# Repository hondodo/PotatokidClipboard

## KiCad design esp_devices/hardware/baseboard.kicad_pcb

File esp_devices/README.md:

# ESP 设备

本目录存放 Potatokid 自研 ESP32 小屏的设备固件与操作文档。后续新增的 ESP 设备统一放在 `firmware/<设备名>/` 下。

```
esp_devices/
├── README.md                       # 本文档
├── .gitignore                      # 排除 secrets.h / 构建产物
└── firmware/
    └── potatokid_esp/              # ESP32-S3 + 1.3" OLED 小屏
        ├── potatokid_esp.ino       # 固件（Arduino）
        ├── secrets.h.example       # 私密配置模板
        └── secrets.h               # 本地私密配置（不入库）
```

## 1. 硬件

| 项目 | 型号 / 参数 |
|---|---|
| 主控 | ESP32-S3（QFN56 rev0.2，16MB Flash，8MB PSRAM） |
| 串口 | CH343 USB-UART，Linux 下为 `/dev/ttyACM0` |
| 屏幕 | 1.3 寸 OLED，**SH1106** 128x64，I2C，地址 `0x3C` |
| 按键 | 可选 1~8 个轻触按键或干接点；当前面板占用 GPIO4/5/6/7/10/11/12/13 |
| 人体感应 | 可选，输出高电平的人体感应模块（VCC 2.7–12V），OUT 接空闲 RTC GPIO（本版 GPIO7 已被按键占用） |
| 音频 | INMP441 麦克风（I2S 14/15/16）+ MAX98357 功放（I2S 17/18/47），两路独立 |
| 遥控 | 433 接收模块（ASL430D 等，串口模式）D0/TX 接 GPIO21 |

## 2. 接线

### 2.1 屏幕

四根杜邦线，**接线前先断开 USB**：

| OLED 模块 | 接到开发板 |
|---|---|
| VCC | **3V3**（不要接 5V） |
| GND | GND |
| SCL | GPIO9 |
| SDA | GPIO8 |

注意事项：

- 按模块丝印接，不同厂家 4 针顺序不一定是 VCC/GND/SCL/SDA；
- ESP32-S3 没有 GPIO22~25，别照抄 ESP32 老教程；GPIO33~37 被 PSRAM 占用，GPIO19/20 是 USB，都要避开；
- 换引脚只改固件顶部的 `PIN_SDA` / `PIN_SCL` 两个常量；
- 模块自带 4.7k 上拉，杜邦线尽量短。

### 2.2 按键（测试期用杜邦线即可）

当前面板的 8 个槽位与引脚：

| 槽位 | 1 | 2 | 3 | 4 | 5 | 6 | 7 | 8 |
|---|---|---|---|---|---|---|---|---|
| GPIO | 4 | 5 | 6 | 7 | 10 | 11 | 12 | 13 |

槽位和 GPIO 可在设备设置页修改（留空或 `-1` = 停用），保存在 NVS。固件把按键脚配置为 `INPUT_PULLUP`，**按下 = 低电平**；没有按键时，一根杜邦线一头插 GPIO、另一头碰 GND 就是一次「按下」。

> 2.4/2.5 的音频 I2S（14~18、47）和 433（21）是固定预留脚，设置页会拒绝再把这些脚配成按键/人体感应。

> GPIO 只做信号输入，**不要**把负载（灯、继电器线圈）直接串在 GPIO 上，也不要给 GPIO 灌 5V。

### 2.3 人体感应（可选，熄屏用）

| 模块 | 接到开发板 |
|---|---|
| VCC | **3V3**（模块支持 2.7–12V；接 3.3V 供电时 OUT 高电平就是 3.3V，不会超压） |
| GND | GND（必须与开发板共地） |
| OUT | GPIO7（可在设备设置页改，`-1` = 未接） |

- 模块「有人输出高电平」；固件读到高电平就亮屏，并把计时重置，人持续在就一直亮，人走后才开始倒计时。
- 熄屏时长在 Admin → ESP 设备 →「④ 翻页与安全 → 熄屏（人体感应）」里选（默认常亮）；改完设备下次心跳生效。
- 熄屏是给面板发 power save（关显示，约省 18mA），不是断 WiFi；屏灭期间只保留 60 秒心跳、不拉页面，有人时立刻唤醒并刷新。
- 模块上电通常要几十秒预热，期间输出可能乱跳，属正常现象。
- 不要接 5V 再把 OUT 直接进 GPIO：ESP32-S3 的 IO 不耐 5V。
- 本版 GPIO7 已作为按键槽位 4，PIR 需改到其它空闲 RTC GPIO（0~21）；14~18/21 已被音频与 433 预留，接线前先确认还有可用脚。

### 2.4 音频（INMP441 麦克风 + MAX98357 功放）

两路独立 I2S，不共用时钟：

| 用途 | 开发板引脚 |
|---|---|
| 麦克风 SCK / WS / SD | GPIO14 / GPIO15 / GPIO16 |
| 功放 BCLK / LRC / DIN | GPIO17 / GPIO18 / GPIO47 |

INMP441：

| INMP441 | 接到 |
|---|---|
| VDD | **3V3**（不要接 5V） |
| GND | GND |
| L/R | **GND**（左声道；不能悬空） |
| SCK | GPIO14 |
| WS | GPIO15 |
| SD | GPIO16（麦克风数据输出） |

MAX98357：

| MAX98357 | 接到 |
|---|---|
| VIN | **5V**（3.3V 也能响，但音量和功率小很多） |
| GND | GND（与开发板共地） |
| BCLK | GPIO17 |
| LRC | GPIO18 |
| DIN | GPIO47 |
| SD | **3V3**（必须接高电平使能；这块板内部下拉，悬空会静音。此 SD 是 shutdown，不是麦克风的数据脚） |
| GAIN | 悬空 9dB / 接 GND 15dB / 接 VDD 3dB |
| + / − | 4Ω 或 8Ω 喇叭（BTL 差分，两根线都不能接地） |

- 功放 VIN 旁并 470~1000µF 电解 + 0.1µF，麦克风 VDD 旁 10µF + 0.1µF；3W 峰值可能到 1A，USB 供电不够时用单独 5V 并共地。
- I2S 时钟线尽量短（10cm 内），喇叭线双绞并远离 433 天线/接收模块与麦克风。
- **录音按键**：后台「ESP 设备」页把某个按键的动作类型选为「录音」，设备上按住 0.7 秒开始录音，松开（或 15 秒上限）后自动上传 16kHz/16bit 单声道 WAV；后台同页底部「最近录音」可直接试听，每台设备保留最近 20 条。
- **语音播放**：后台 ESP 设备页的「最近录音」里点「设备播放」，或选一个 PCM WAV（≤2MB）上传，服务端会把它排进该设备队列；设备每 5 秒轮询一次，取到后下载播放，播完回报删除。队列每台设备最多 5 条、10 分钟没取走自动过期。
  - 音量：后台「④ 翻页与安全 → 语音音量」0~100（默认 70），随心跳下发，最迟 60 秒生效，不用重启。
  - 存储：录音与播放文件都转发到 yuntu（`datas/forward_config.json` 的 baseUrl / serviceToken），后台列表从 yuntu 读取，设备拿 7 天有效的签名直链下载；转发失败才保留本地副本。改地址或令牌只改这个 JSON，不用重启。
  - 状态：后台面板显示「排队中 / 下载中 / 播放中」，播完自动刷新录音列表；设备屏幕显示「语音 · 下载中… / 播放中」，播完自动回到页面。
  - MAX98357 的 SD 必须接 3V3（悬空会静音，实测过），GAIN 悬空为 9dB。
- 模块自带去耦与滤波，台面测试不用再并 470~1000µF；只有长导线、满功率 3W 或共用弱 USB 供电导致重启时，才需要在 VIN 旁补大电容。

### 2.5 433 遥控（串口模式）

用 ASL430D 这类「学习型 4 路解码」接收板，**切到串口模式**后不用对码，任何 EV1527 系遥控器的按键都能解出 24bit 编码（前 20 位地址 + 后 4 位按键码），一个遥控器就能配出多个不同动作。

| 模块 | 接到 |
|---|---|
| VCC | **3V3**（不要 5V，输出高电平会超压） |
| GND | GND |
| **D0(TX)** | **GPIO21**（UART1 RX，9600 8N1） |
| ANT | 弹簧天线，尽量拉直 |
| D1/D2/D3/KEY | 悬空 |

切模式：**按住板上 KEY 再上电**，松手后指示灯闪 **4 次** 即串口模式（闪 1 次点动高、2 次自锁、3 次互锁、5 次点动低）。

后台配置：ESP 设备页 →「433 遥控」→「学习」→ 按一下遥控器，编码自动填入 → 选动作（系统动作 / HA 动作 / 手动控制）→「保存」。设备的屏幕在未绑定时会显示收到的编码，方便对照。

- GPIO21 是 RTC GPIO，深睡可用 EXT1 唤醒（GPIO47/48 不行）；靠遥控唤醒时接收模块必须持续供电。
- 4 路解码模式（D0~D3 各自输出高低）每路只能对应一个键，最多 4 个键；串口模式只占 D0 一根线，按编码区分，键数不受限制。
- 天线按 433.92MHz 的 1/4 波长留约 17cm，拉直并远离功放、喇叭线和 I2S 时钟。

## 3. 开发环境

本机已装好 `arduino-cli 1.6.0` + ESP32 core `3.3.12` + `U8g2 2.36.19`，正常的编译烧录不需要联网。

国内网络直连 GitHub 基本不可用（工具链下载会超时）。重装环境时用代理索引 + 只装 S3 需要的工具：

```bash
# 1) 安装 arduino-cli
mkdir -p ~/.local/bin
curl -fsSL https://downloads.arduino.cc/arduino-cli/arduino-cli_latest_Linux_64bit.tar.gz \
  -o /tmp/arduino-cli.tgz
tar -xzf /tmp/arduino-cli.tgz -C ~/.local/bin arduino-cli

# 2) 安装核心与库
~/.local/bin/arduino-cli core install esp32:esp32
~/.local/bin/arduino-cli lib install U8g2
```

> 如果 `core install` 卡在 github.com 下载工具链：把索引里的 `https://github.com/` 换成
> `https://ghfast.top/https://github.com/`，并删掉 riscv 工具链、其它芯片 libs 等 S3 用不到的
> 依赖，用 `--config-file` 指向改造后的本地索引再安装。

## 4. 编译与烧录

```bash
~/.local/bin/arduino-cli compile --upload -p /dev/ttyACM0 \
  --fqbn esp32:esp32:esp32s3:FlashSize=16M,PSRAM=opi,CDCOnBoot=default,UploadSpeed=921600,PartitionScheme=no_fs \
  /home/honghao/codes/PotatokidClipboard/esp_devices/firmware/potatokid_esp
```

板卡选项说明：

| 选项 | 值 | 原因 |
|---|---|---|
| `FlashSize` | `16M` | 模组 16MB |
| `PSRAM` | `opi` | WROOM-2 系列 8MB PSRAM |
| `CDCOnBoot` | `default`（关闭） | 走 CH343 串口，Serial 输出到 UART0 |
| `UploadSpeed` | `921600` | CH343 稳定档位 |
| `PartitionScheme` | `no_fs` | app0/app1 各 2MB（双 OTA 槽）。默认分区只有 1.25MB，装不下中文字库；`huge_app` 有 3MB 但没有 OTA 槽 |

`no_fs` 没有文件系统分区，本项目不用；NVS 起始地址不变，换分区后 WiFi / 控制端地址等配置都保留。
**首次从其它分区方案切换时仍需 USB 烧录一次**，之后即可远程 OTA。

串口日志：

```bash
~/.local/bin/arduino-cli monitor -p /dev/ttyACM0 -c baudrate=115200
```

## 5. 私密配置

```bash
cp firmware/potatokid_esp/secrets.h.example firmware/potatokid_esp/secrets.h
# 编辑 secrets.h 填 WiFi 名称/密码、局域网设置页口令
```

`secrets.h` 已在 `.gitignore` 中排除，**不要提交真实密码**。缺失该文件时编译会直接报错，属预期行为。

## 6. 运行行为

1. 上电读取 NVS 中保存的 WiFi 与控制端地址，首次运行用 `secrets.h` 与固件默认值；
2. 15 秒内连上：OLED 显示 `IP / srv ok / 信号`，向服务端注册并拉取已放行的控制项；
3. 连不上：自动开热点 `Potatokid-Screen-Setup`（无密码），手机连上后浏览器打开
   `http://192.168.4.1` 配网，配置写入 NVS 后自动重启；
4. 联网期间每 60 秒心跳一次，并顺带刷新控制项列表、检查服务端是否发布了新固件；掉线超过 60 秒转配网热点；
5. 局域网内访问 `http://<设备IP>/` 可改 WiFi，`/settings` 是设置页，都需要口令（`secrets.h` 的网页账号/密码）。

> ⚠️ **状态栏 IP 必须是真实值，禁止写死假 IP**
>
> 屏幕顶部状态栏中间显示的设备 IP，**必须取自 `WiFi.localIP()` 的真实 station IP**。
> 在 WiFi 连上、拿到 IP **之前该位置留空**，绝不显示任何占位/示例地址。
>
> 规划原型 `docs/esp-screen-admin-prototype.html` 与 `docs/esp-screen-display-prototype.html`
> 里写的 `192.168.1.123` **只是演示用的假值**，落地固件时**不要照抄**。
> 断网态画 ✗、配网态画 AP，这两种状态同样不显示 IP。

### 6.1 屏幕四行显示与设备类型字典（oled-2.0+）

固件保持「哑巴」：不认识任何设备类型，只显示服务端下发的**四行纯文本**。设备在 Admin 页
显式声明 `deviceType` + 显示实体绑定，服务端按共享字典（`pscreen_server/server/deviceTypes.js`，
与 home 端共用）把 HA 状态解析成四行下发，新设备类型接入**不用重烧固件**。

- `GET /api/device/esp/actions?format=text&deviceId=...&page=N` 的返回：
  - 第一行固定 `DISPLAY|标题|主状态|副状态|按键提示`（服务端解析好的纯文本）；
  - 其后每行 `button|name|entityId|action|id` 是放行的控制项（旧固件忽略 DISPLAY 行，仍可读按键行）。
- 屏幕布局：顶部状态栏固定「页码 + 真实 IP + WiFi 信号格」，下面依次标题 / 主状态 /
  副状态 / 按键提示四行。主状态异常时用**反白块**（亮底黑字）强调——单色屏唯一的重点手段。
- **单色三色通用**：实物有蓝光 / 白光 / 黄光三种屏，但每像素只有亮/灭两级，没有灰阶。
  绘制只用单一亮色，层次靠字号 + 留白 + 反白；不画灰阶、不画虚线。`screenColor`（NVS, 0蓝/1白/2黄）
  仅记录色别，三色 firmware 绘制逻辑一致。
- **跑马灯**：文字放得下就静止，放不下才无缝循环滚动；四行独立相位、速度
  标题 0.45× → 主状态 0.75× → 副状态 1.1× → 按键提示 1.6×（基准 15px/s），各行不同步。
  以 ~10fps 推进相位，仅超长时重绘，不整屏高频刷新（避免拖慢 I2C / 心跳 / 按键轮询）。
- **翻页**：按键绑 `next_page` / `prev_page` / `home_page` 系统动作时，服务端回执 `sys`，
  固件维护 `currentPage` 并重新拉取该页四行文本与按键定义。按键硬件可扩展（当前 3 键）。
- **中文字库**：主屏用 `wqy12_t_gb2312` + `drawUTF8`；缺字可按 README 前文换 `chinese2/3` 字库。

## 7. 设置页（设备本地）

`http://<设备IP>/settings`：

| 项 | 说明 |
|---|---|
| 控制端地址 | 默认 `http://ptool.w1.luyouxia.net`，存 NVS，改完自动重启。换域名 / 换服务端只改这里，不用重新烧录；留空保存恢复默认 |
| 可控设备列表 | 从服务端读取**已放行**的控制项（名称 / HA 实体 / 动作 / 按钮），每行可点「测试」直接执行一次 |
| 物理按键 | GPIO4/5/6 对应按钮1/2/3，短接 GND 即触发 |
| 固件升级 | 显示当前版本；服务端发布新版本时显示新版本号、大小、更新说明和「立即升级」按钮 |
| 自动更新 | 勾选后设备检测到新版本会自行下载安装（约 20 秒），完成后自动重启；开关存 NVS，不重启生效 |

屏幕上会短暂显示按键结果（`sent ok` / `failed, see serial`），失败原因看串口日志。

## 8. 用按键控制 HA（白名单在服务端）

固件本身不存 HA 地址和令牌，按键只发请求给 pscreen_server，由服务端按白名单代调 HA：

1. 管理页 `/admin` → **设备状态** → 找到这台 ESP（类型为空、型号 `ESP32-S3 1.3 OLED`）→「ESP 控制」；
2. 添加控制项：显示名、实体 id（如 `light.living_room`）、动作（切换/开/关/执行）、绑定的按钮槽位；
3. 勾选「放行」——**只有勾选的项才会下发到设备**，没勾的设备看不到、也调不动；
4. 右上角「HA 连接」填 HA 地址与长期访问令牌（HA：用户资料 → 长期访问令牌）。令牌只存在服务端，不下发到 ESP。

服务端接口（设备侧无需鉴权，白名单是唯一门禁）：

| 用途 | 接口 | 返回 |
|---|---|---|
| 拉取放行项 | `GET /api/device/esp/actions?deviceId=<id>&format=text` | `button\|name\|entityId\|action\|id` 每行一项 |
| 按键触发 | `POST /api/device/esp/press`，body `{deviceId, button}` 或 `{deviceId, actionId}` | HA 执行结果 |

管理页接口（需登录）：`GET/PUT /api/admin/machines/:id/esp`、`GET/PUT /api/admin/ha`。

> 动作与 HA 服务的对应：`toggle → <domain>.toggle`、`turn_on → <domain>.turn_on`、`turn_off → <domain>.turn_off`、
> `run → <domain>.turn_on`（用于 script / scene）。窗帘这类需要 `open_cover/close_cover` 的实体，建议在 HA 里建 script 后用「执行」。

### 显示模板占位符

「ESP 设备分类 → 页面 → 主状态/副状态模板」里可写以下令牌，前端预览与服务端下发用同一套解析：

| 令牌 | 取值 |
|---|---|
| `{main}` / `{s1}` / `{s2}` | 三个绑定实体（按设备类型字典的属性） |
| `{title}` / `{名称}` | 页面名 |
| `{domain.entity_id}` | 该实体的 state，如 `{switch.bedroom}` |
| `{domain.entity_id.attr}` | 该实体的指定属性，缺失时回落 state，如 `{climate.bed.temperature}` |

属性段让 128×64 屏能同时显示当前值与目标值，例如空调：

```
{climate.xiaomi_cn_735376016_m9} 当前{climate.xiaomi_cn_735376016_m9.current_temperature}° 目标{climate.xiaomi_cn_735376016_m9.temperature}°
```

超宽由固件按各行节拍走马灯滚动；预览只显示首屏。遥控设备的三段令牌 `{remote.<设备id>.<字段>}` 仍走本地实时状态，不查 HA。

## 9. 控制真实设备（继电器）

GPIO 只有 3.3V / 几 mA，只能给信号，不能直接带负载。常规做法：

| 继电器模块 | 接到 |
|---|---|
| VCC | 开发板 5V（或外部 5V，与开发板共地） |
| GND | GND（必须与开发板共地） |
| IN | GPIO4（对应按钮1） |
| COM / NO | 串在被控设备的火线或信号线上 |

- 模块分「高电平触发 / 低电平触发」两种，固件按键是低电平有效；若模块是高电平触发，接 `IN` 后行为会相反，换低电平触发模块或把按键改成上拉对 VCC（改固件 `INPUT_PULLDOWN` + 高电平判断）；
- 强烈建议被控设备的强电部分由**成品继电器/智能插座**承担，ESP 只做触发，避免市电接线风险；
- 不想接继电器时，直接用「ESP 按键 + HA 控制」的方式验证链路：HA 里操作灯/插座，设备只负责发按键请求。

## 10. 远程升级（OTA）

设备每 60 秒心跳时会顺带问服务端「有没有新固件」。检测到版本不同 → 屏幕标题变成
`Update ready`（显示当前/新版本并提示 `open web page`），用户打开设备的
`http://<设备IP>/settings` → 「固件升级」→「立即升级」即可，升级时屏幕显示百分比，
完成后自动重启，WiFi 与控制端地址配置都保留。

**发布流程**：

1. 改代码，并把 `APP_VER` 改成新版本号（如 `oled-1.4`）；
2. 编译导出 bin（OTA 只需要 app 镜像，不要 `merged.bin`）：

   ```bash
   ~/.local/bin/arduino-cli compile \
     --fqbn esp32:esp32:esp32s3:FlashSize=16M,PSRAM=opi,CDCOnBoot=default,UploadSpeed=921600,PartitionScheme=no_fs \
     --output-dir /tmp/fw_out \
     /home/honghao/codes/PotatokidClipboard/esp_devices/firmware/potatokid_esp
   # 产物：/tmp/fw_out/potatokid_esp.ino.bin
   ```

3. 管理页 `/admin` → **设备状态** → 「固件升级」→ 选 `potatokid_esp.ino.bin`，
   填与 `APP_VER` **完全一致**的版本号 →「上传并发布」；
4. 设备下一次心跳（≤60 秒）就会提示可更新；「撤回发布」可让设备停止提示。

**自动更新**（适合远程设备，不用每次回后台点按钮）：

- 设备设置页「固件升级」里勾选「自动更新」，开关存 NVS，保存即生效（不需要重启）；
- 心跳发现新版本后延迟 8 秒开始自动安装，屏幕显示 `Update ready` → `Updating xx%` → 自动重启；
- 失败保留当前固件，30 分钟后重试；同一版本不会陷入「失败-重启-再失败」的循环；
- 设备只比对版本字符串，**服务端发布什么版本就装什么**（发布旧版本等于自动回滚），发布前确认版本号；
- 自动更新依赖设备能访问「控制端地址」，离线设备不会触发，恢复在线后下一次心跳补上。

注意：

- 版本号必须与固件内 `APP_VER` 一致，否则升级后仍会提示（设备只做字符串比对）；
- OTA 依赖双 app 槽，`no_fs`/`min_spiffs` 可用，`huge_app` 不行；
- 升级中途断电不会变砖：旧固件仍在另一个槽，重新上电会回滚；
- 设备侧接口：`GET /api/device/firmware/latest?format=text` → `version|size|sha256|notes`，
  `GET /api/device/firmware/download` 下载 bin。

## 11. 常见问题

| 现象 | 排查 |
|---|---|
| 屏幕全黑 | 先看串口是否打印 `OLED ready at 0x3C`；没有则检查 SDA/SCL 是否接反、VCC 是否为 3V3 |
| 屏幕花屏/错位（左缺右乱码） | 面板是 SH1106 而驱动写成 SSD1306；用 `U8G2_SH1106_128X64_NONAME_F_HW_I2C`（当前固件已如此） |
| 亮屏后正文空白、只剩顶栏页码和 IP | ≤`oled-3.2` 的 bug：`NetSnapshot` 标量未初始化，感应心跳那条不拉页面的路径会发布「状态沿用上一轮、文本全空」的假快照，把正文刷成空白。`oled-3.3` 已修（补默认值 + 感应上报不再顺延 60 秒心跳） |
| 按键名称显示乱码 | 控制项名是中文，必须用 UTF-8 中文字库 + `drawUTF8`（当前固件用 `u8g2_font_wqy12_t_gb2312`）；生僻字不在 GB2312 内可换 `u8g2_font_wqy12_t_chinese2/3` |
| 设置页没有「立即升级」 | 服务端还没发布固件（admin →「固件升级」上传），或已发布版本与设备 `APP_VER` 相同 |
| 升级失败 | 看串口 `[ota] failed code=...`；常见是分区不是 `no_fs`/`min_spiffs`（无双槽）、服务端 bin 被撤回、设备访问不到控制端地址 |
| 串口无输出 | 确认板卡选项 `CDCOnBoot=default`，端口为 `/dev/ttyACM0` |
| 连不上 WiFi | 只支持 2.4GHz；确认热点名称密码；等 15 秒自动进配网热点 |
| 局域网设置页打不开 | 需要 Basic Auth（`secrets.h` 的口令）；确认设备和电脑在同一网段 |
| 服务端显示离线 | 检查控制端地址是否可达、心跳日志 `[srv] ... -> HTTP 200 ok` |
| 设置页控制项为空 | 管理页还没添加控制项，或没勾「放行」 |
| 按键提示 failed | 看串口：`未配置 HA` → 填 HA 连接；`调用 HA 失败` → 检查 HA 地址/令牌；`未放行` → 回管理页勾选 |

## 11. 新增 ESP 设备的约定

- 目录：`firmware/<设备名>/<设备名>.ino`，与 Arduino sketch 同名规则保持一致；
- 私密信息一律走 `secrets.h`（模板入库、真实文件不入库）；
- `deviceId` 建议 `<前缀>-<MAC 12 位>`，前缀区分设备形态（如 `esp32s3`）；
- 上线后统一调 `/api/device/register` 与 `/api/device/heartbeat`，不要另建注册接口；
- 需要 HA 控制的设备，复用 `/api/device/esp/actions` 与 `/api/device/esp/press`，白名单统一在 admin 页维护；
- 新增硬件引脚在 README 的接线表登记，避免后续换板接错。

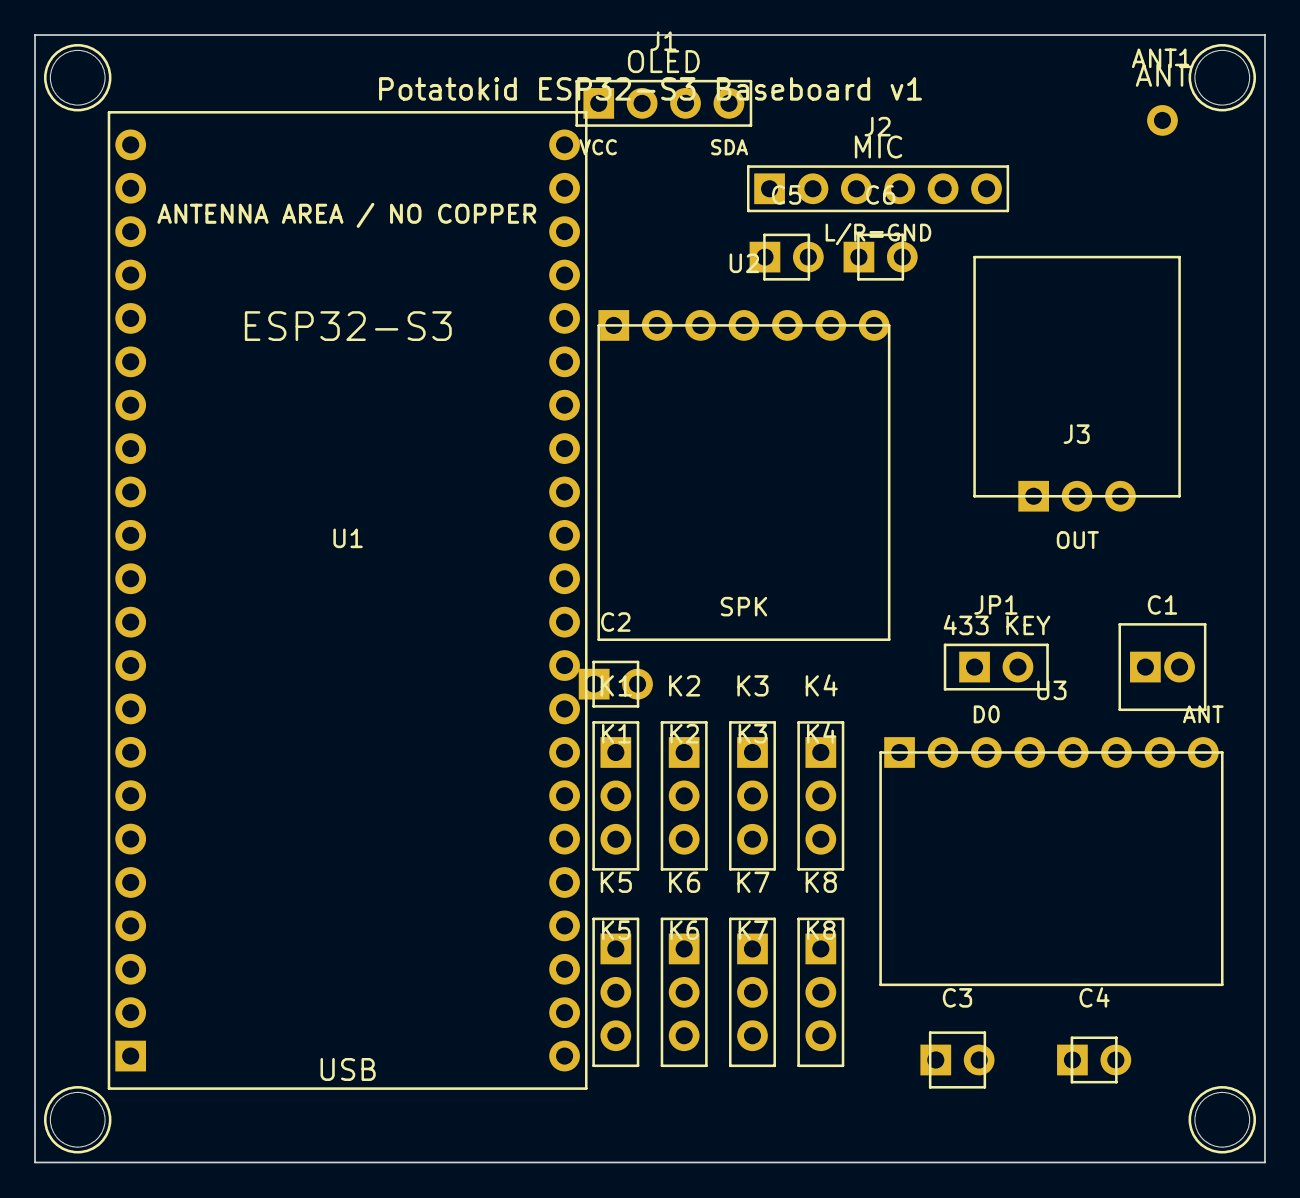
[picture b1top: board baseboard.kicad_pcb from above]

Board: 2 copper layers, 72.0 x 66.0 mm, 26 parts (0 on the bottom side), 23 nets, no tracks yet.

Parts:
ANT1: ANT-17cm
C1: 470uF/10V
C2, C4, C5, C6: 0.1uF
C3: 10uF
H1, H2, H3, H4: M3; MountingHole-M3
J1: OLED-4P
J2: INMP441-6P
J3: PIR-SR301
JP1: RF-KEY-JUMP
K1, K2, K3, K4, K5, K6, K7, K8: KEY-3P
U1: ESP32-S3-DevKitC-1
U2: MAX98357A
U3: ASL430D-433RX

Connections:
3V3: C3.1, C4.1, C5.1, C6.1, J1.1, J2.1, J3.3, U1.21, U1.22, U2.5, U3.2
5V: C1.1, C2.1, U1.2, U2.7
AMP_BCLK: U1.13, U2.2
AMP_DIN: U1.28, U2.3
AMP_LRC: U1.12, U2.1
GND: C1.2, C2.2, C3.2, C4.2, C5.2, C6.2, J1.2, J2.2, J2.6, J3.1, JP1.2, K1.3, K2.3, K3.3, K4.3, K5.3, K6.3, K7.3, K8.3, U1.1, U1.23, U1.24, U1.44, U2.6, U3.1
KEY1: K1.1, U1.19
KEY2: K2.1, U1.18
KEY3: K3.1, U1.17
KEY4: K4.1, U1.16
KEY5: K5.1, U1.7
KEY6: K6.1, U1.6
KEY7: K7.1, U1.5
KEY8: K8.1, U1.4
MIC_SCK: J2.3, U1.3
MIC_SD: J2.5, U1.14
MIC_WS: J2.4, U1.15
PIR_OUT: J3.2, U1.35
RF_ANT: ANT1.1, U3.8
RF_D0: U1.27, U3.3
RF_KEY: JP1.1, U3.7
SCL: J1.3, U1.8
SDA: J1.4, U1.11

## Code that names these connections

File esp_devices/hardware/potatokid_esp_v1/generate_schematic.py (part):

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    "GPIO4": "BTN1", "GPIO5": "BTN2", "GPIO6": "BTN3", "GPIO7": "BTN4",
    "GPIO10": "BTN5", "GPIO11": "BTN6", "GPIO12": "BTN7", "GPIO13": "BTN8",
    "GPIO8": "OLED_SDA", "GPIO9": "OLED_SCL",
    "GPIO14": "MIC_SCK", "GPIO15": "MIC_WS", "GPIO16": "MIC_SD",
    "GPIO17": "AMP_BCLK", "GPIO18": "AMP_LRC", "GPIO47": "AMP_DIN",
    "GPIO21": "RF433_DATA",
})

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        "MAX98357 SD must be tied to 3V3 (module has internal pull-down). GAIN left open = 9dB.",
        "INMP441 L/R tied to GND (left channel). Speaker is BTL differential: never tie either terminal to GND.",
        "Buttons are active-low with INPUT_PULLUP: pressed = 0V. Do not feed 5V into any GPIO.",
        "PIR_OUT is intentionally unassigned: GPIO7 is button slot 4. Pick a free RTC GPIO (0-21) in JLCEDA.",
        "Capacitors C1-C4 are optional; modules already have on-board decoupling.",
        "Before PCB: assign footprints, run ERC, and verify the board header pin order against your physical board.",
    ]
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        for comp in COMPONENTS:
            note = ""
            if comp["ref"] == "J4":
                note = "Optional; assign a free RTC GPIO for PIR_OUT"
            elif comp["ref"] == "J3":
                note = "GAIN open = 9dB; SD tied to 3V3"
            elif comp["ref"].startswith("C"):
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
